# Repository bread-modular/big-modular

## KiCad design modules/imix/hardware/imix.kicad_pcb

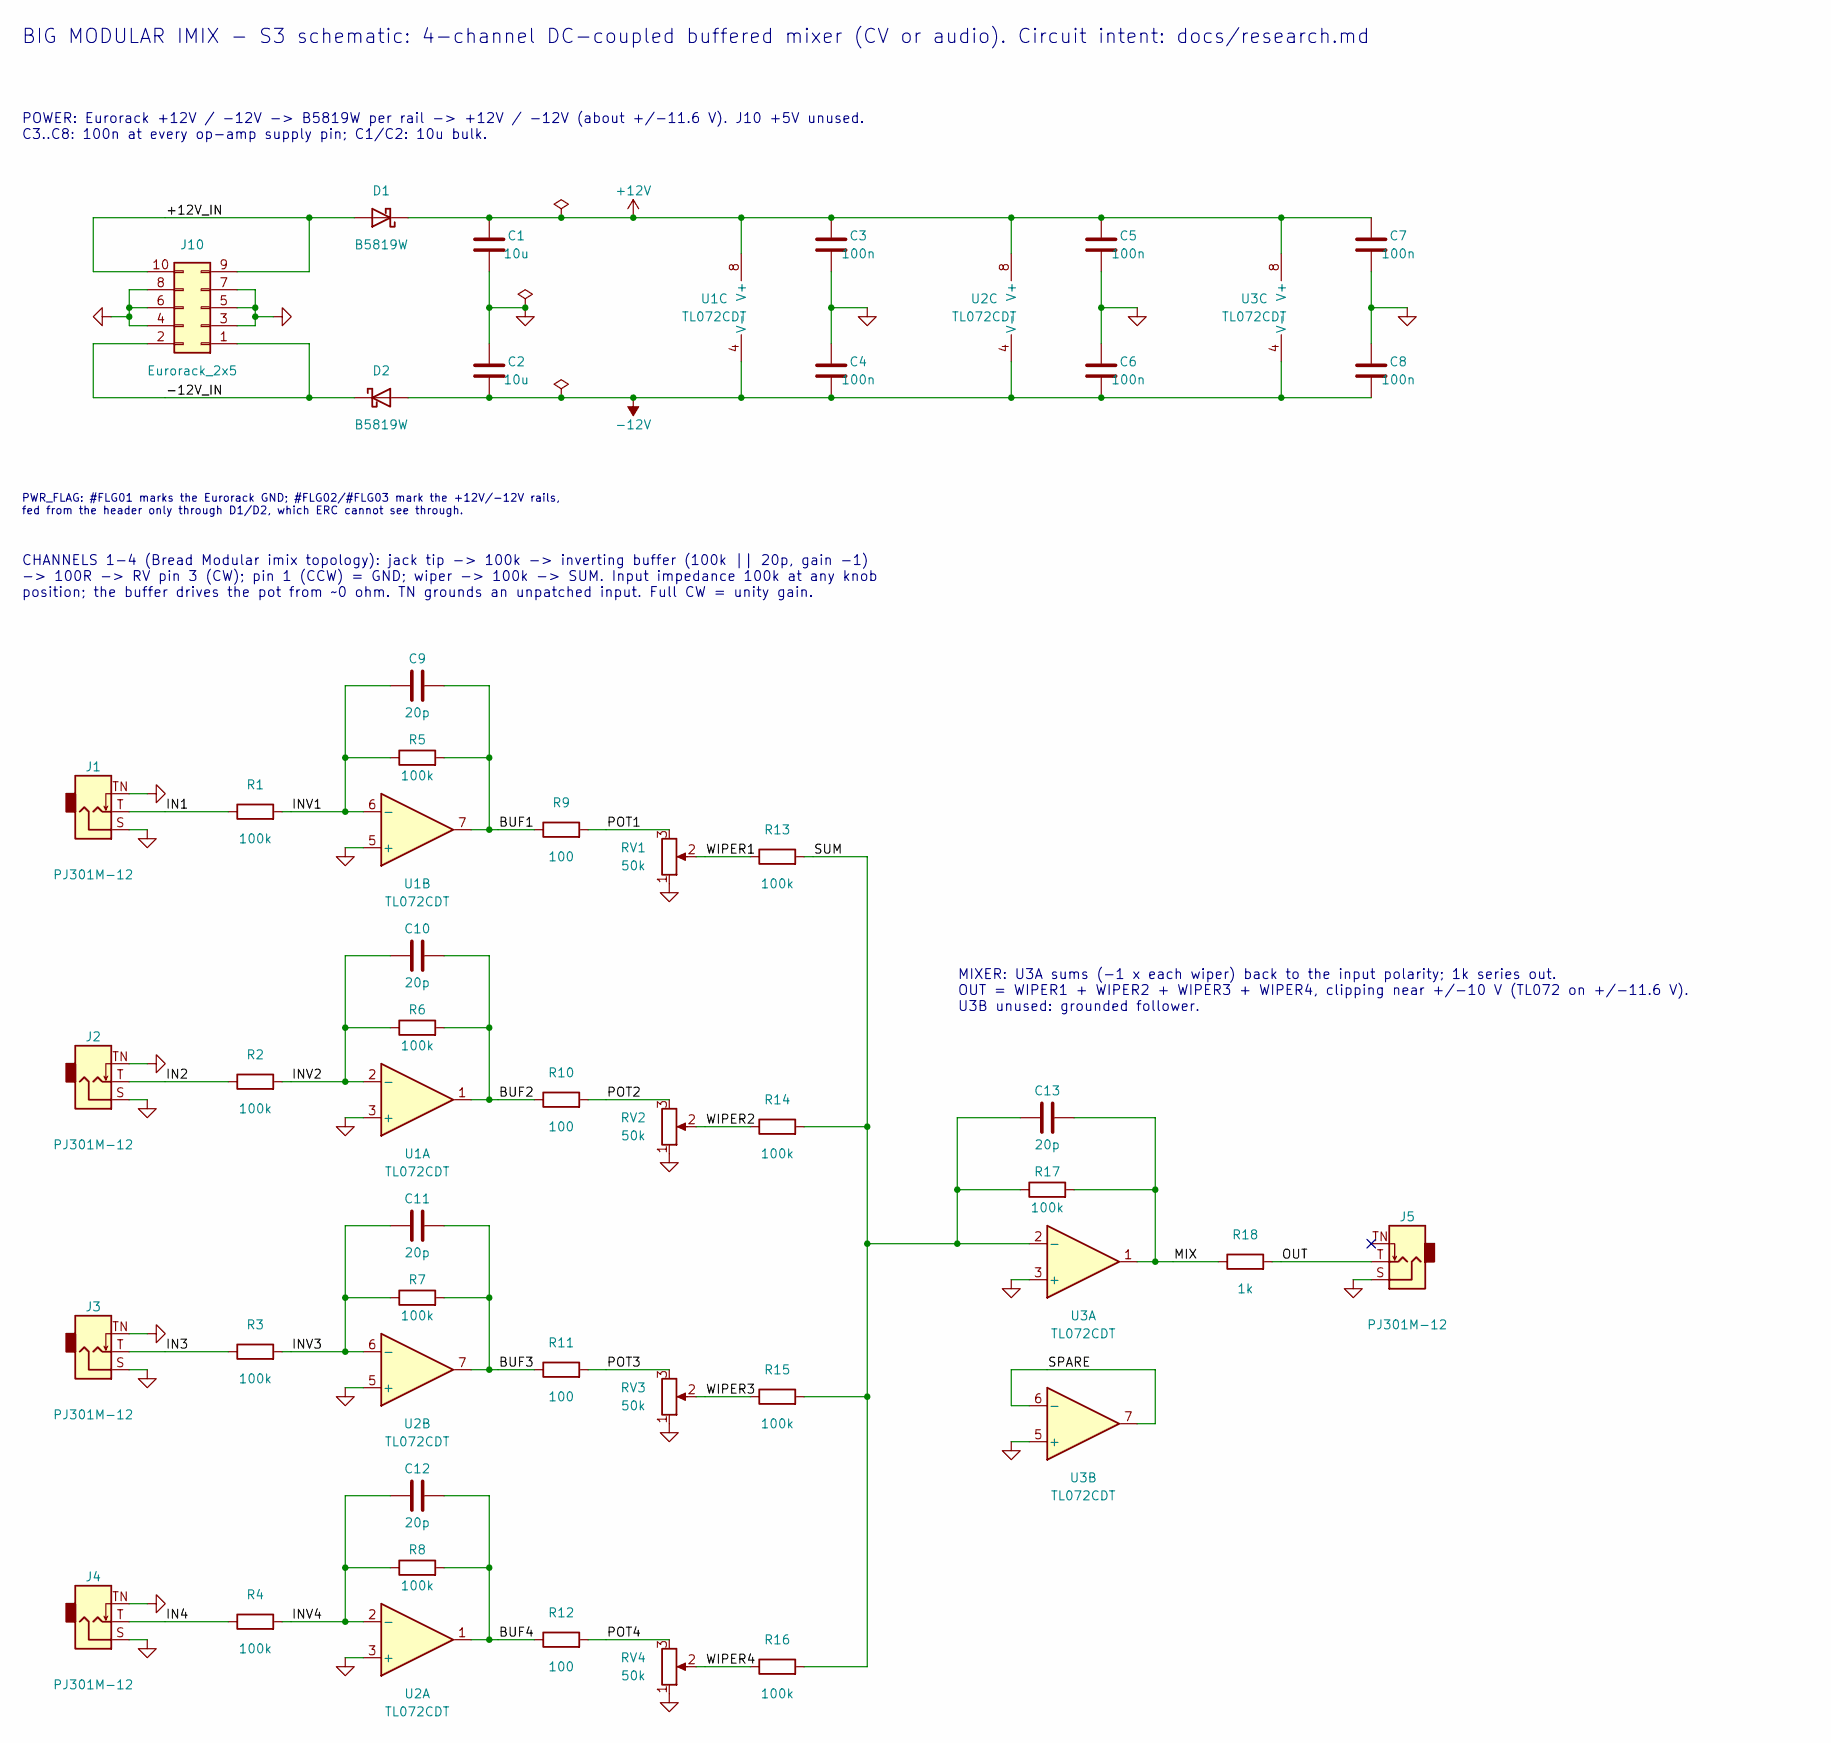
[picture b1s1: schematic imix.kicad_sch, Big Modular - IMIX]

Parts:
C1, C2: 10u; C_0805_2012Metric; Voltage 25V; MPN CL21A106KAYNNNE; LCSC C15850
C3, C4, C5, C6, C7, C8: 100n; C_0603_1608Metric; Voltage 50V; MPN CC0603KRX7R9BB104; LCSC C14663
C9, C10, C11, C12, C13: 20p; C_0603_1608Metric; Voltage 50V; MPN CL10C200JB8NNNC; LCSC C1648
D1, D2: B5819W; D_SOD-123; MPN B5819W SL; LCSC C8598
J1, J2, J3, J4, J5: PJ301M-12; Jack_3.5mm_QingPu_WQP-PJ301M-12_Vertical
J10: Eurorack_2x5; PinHeader_2x05_P2.54mm_Vertical
R1, R2, R3, R4, R5, R6, R7, R8, R13, R14, R15, R16, R17: 100k; R_0603_1608Metric; MPN 0603WAF1003T5E; LCSC C25803
R9, R10, R11, R12: 100; R_0603_1608Metric; MPN 0603WAF1000T5E; LCSC C22775
R18: 1k; R_2512_6332Metric; MPN 25121WF1001T4E; LCSC C54315
RV1, RV2, RV3, RV4: 50k; Potentiometer_RV09
U1, U2, U3: TL072CDT; SOIC-8_3.9x4.9mm_P1.27mm; MPN TL072CDT; LCSC C6961

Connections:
+12V: C1.1, C3.1, C5.1, C7.1, D1.1 (K), U1.8 (V+), U2.8 (V+), U3.8 (V+)
-12V: C2.2, C4.2, C6.2, C8.2, D2.2 (A), U1.4 (V-), U2.4 (V-), U3.4 (V-)
/+12V_IN: D1.2 (A), J10.9, J10.10
/-12V_IN: D2.1 (K), J10.1, J10.2
/BUF1: C9.2, R5.2, R9.1, U1.7
/BUF2: C10.2, R6.2, R10.1, U1.1
/BUF3: C11.2, R7.2, R11.1, U2.7
/BUF4: C12.2, R8.2, R12.1, U2.1
/IN1: J1.T, R1.1
/IN2: J2.T, R2.1
/IN3: J3.T, R3.1
/IN4: J4.T, R4.1
/INV1: C9.1, R1.2, R5.1, U1.6 (-)
/INV2: C10.1, R2.2, R6.1, U1.2 (-)
/INV3: C11.1, R3.2, R7.1, U2.6 (-)
/INV4: C12.1, R4.2, R8.1, U2.2 (-)
/MIX: C13.2, R17.2, R18.1, U3.1
/OUT: J5.T, R18.2
/POT1: R9.2, RV1.3
/POT2: R10.2, RV2.3
/POT3: R11.2, RV3.3
/POT4: R12.2, RV4.3
/SPARE: U3.6 (-), U3.7
/SUM: C13.1, R13.2, R14.2, R15.2, R16.2, R17.1, U3.2 (-)
/WIPER1: R13.1, RV1.2
/WIPER2: R14.1, RV2.2
/WIPER3: R15.1, RV3.2
/WIPER4: R16.1, RV4.2
GND: C1.2, C2.1, C3.2, C4.1, C5.2, C6.1, C7.2, C8.1, J1.S, J1.TN, J2.S, J2.TN, J3.S, J3.TN, J4.S, J4.TN, J5.S, J10.3, J10.4, J10.5, J10.6, J10.7, J10.8, RV1.1, RV2.1, RV3.1, RV4.1, U1.3 (+), U1.5 (+), U2.3 (+), U2.5 (+), U3.3 (+), U3.5 (+)

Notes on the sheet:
MIXER: U3A sums (-1 x each wiper) back to the input polarity; 1k series out. OUT = WIPER1 + WIPER2 + WIPER3 + WIPER4, clipping near +/-10 V (TL072 on +/-11.6 V). U3B unused: grounded follower.
BIG MODULAR IMIX - S3 schematic: 4-channel DC-coupled buffered mixer (CV or audio). Circuit intent: docs/research.md
CHANNELS 1-4 (Bread Modular imix topology): jack tip -> 100k -> inverting buffer (100k || 20p, gain -1) -> 100R -> RV pin 3 (CW); pin 1 (CCW) = GND; wiper -> 100k -> SUM. Input impedance 100k at any knob position; the buffer drives the pot from ~0 ohm. TN grounds an unpatched input. Full CW = unity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
PWR_FLAG: #FLG01 marks the Eurorack GND; #FLG02/#FLG03 mark the +12V/-12V rails, fed from the header only through D1/D2, which ERC cannot see through.
POWER: Eurorack +12V / -12V -> B5819W per rail -> +12V / -12V (about +/-11.6 V). J10 +5V unused. C3..C8: 100n at every op-amp supply pin; C1/C2: 10u bulk.

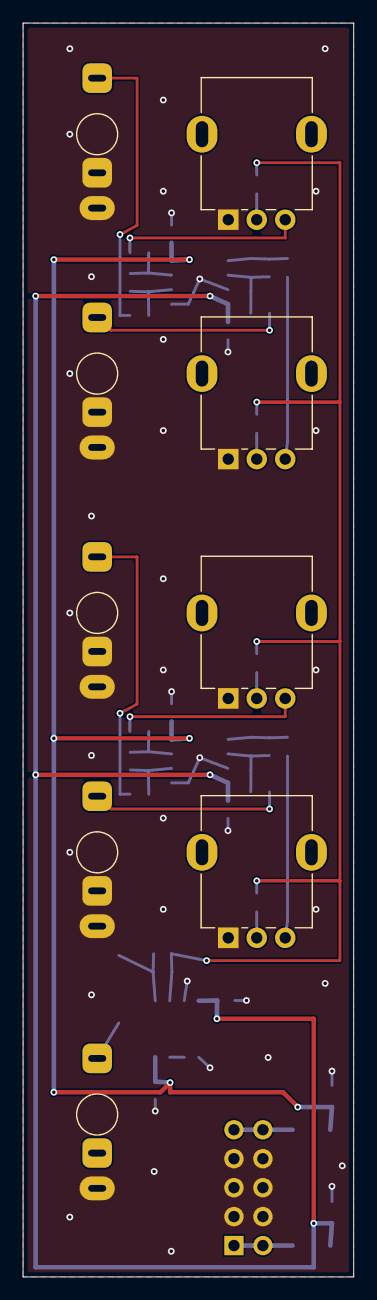
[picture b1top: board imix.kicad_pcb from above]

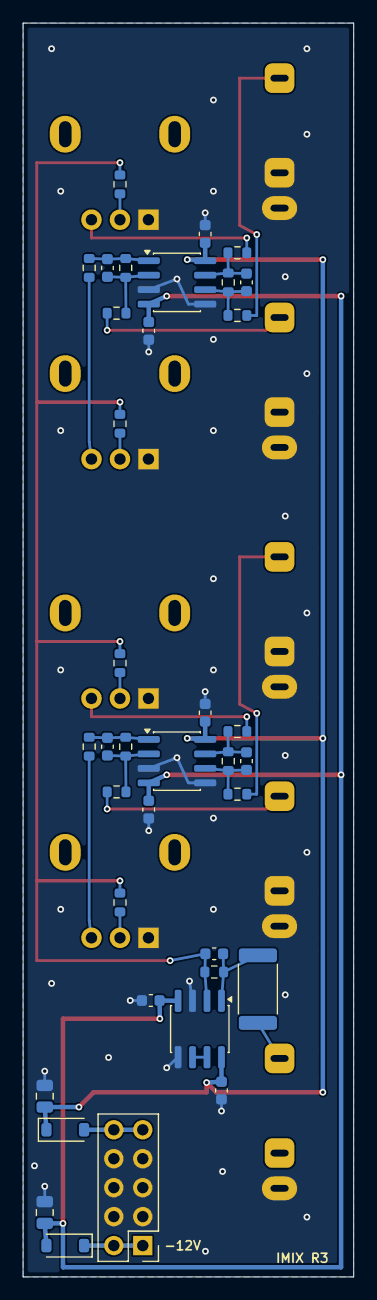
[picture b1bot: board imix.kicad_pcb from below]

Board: 2 copper layers, 29.0 x 110.0 mm, 46 parts (37 on the bottom side), 29 nets.

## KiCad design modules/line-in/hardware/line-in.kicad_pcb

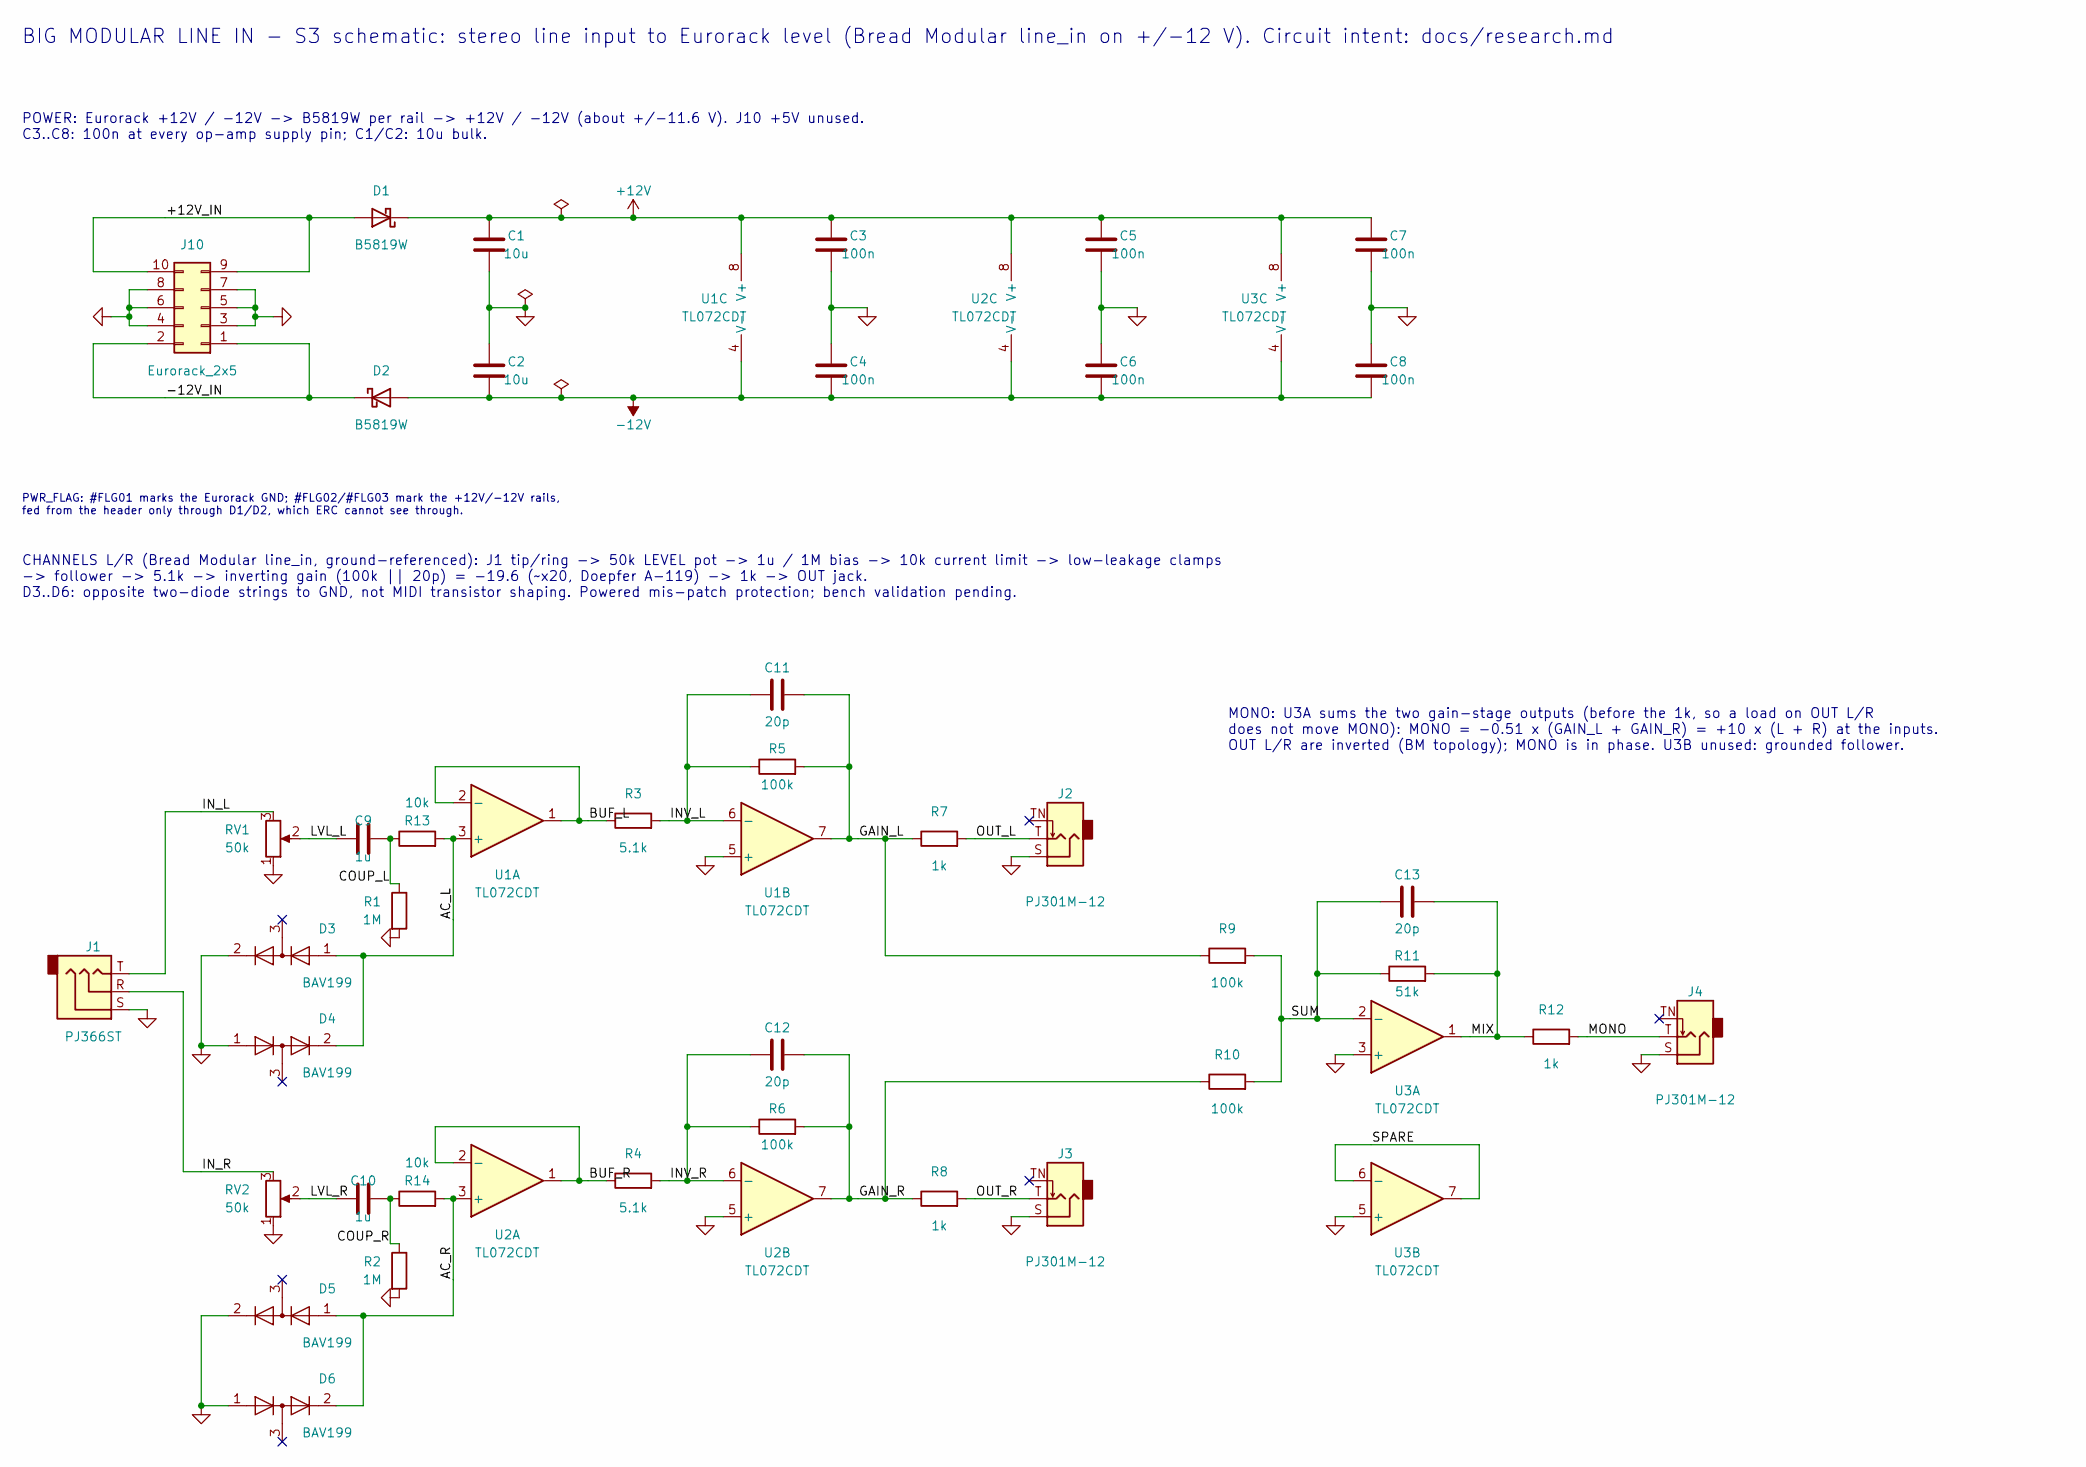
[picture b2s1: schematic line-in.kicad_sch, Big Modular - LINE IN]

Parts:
C1, C2: 10u; C_0805_2012Metric; Voltage 25V; MPN CL21A106KAYNNNE; LCSC C15850
C3, C4, C5, C6, C7, C8: 100n; C_0603_1608Metric; Voltage 50V; MPN CC0603KRX7R9BB104; LCSC C14663
C9, C10: 1u; C_0805_2012Metric; Voltage 50V; MPN CL21B105KBFNNNE; LCSC C28323
C11, C12, C13: 20p; C_0603_1608Metric; Voltage 50V; MPN CL10C200JB8NNNC; LCSC C1648
D1, D2: B5819W; D_SOD-123; MPN B5819W SL; LCSC C8598
D3, D4, D5, D6: BAV199; SOT-23; MPN BAV199,215; LCSC C40919
J1: PJ366ST; Jack_3.5mm_QingPu_WQP-PJ366ST_Vertical
J2, J3, J4: PJ301M-12; Jack_3.5mm_QingPu_WQP-PJ301M-12_Vertical
J10: Eurorack_2x5; PinHeader_2x05_P2.54mm_Vertical
R1, R2: 1M; R_0603_1608Metric; MPN 0603WAF1004T5E; LCSC C22935
R3, R4: 5.1k; R_0603_1608Metric; MPN 0603WAF5101T5E; LCSC C23186
R5, R6, R9, R10: 100k; R_0603_1608Metric; MPN 0603WAF1003T5E; LCSC C25803
R7, R8, R12: 1k; R_1206_3216Metric; MPN ESR18EZPF1001; LCSC C2074262
R11: 51k; R_0603_1608Metric; MPN 0603WAF5102T5E; LCSC C23196
R13, R14: 10k; R_0603_1608Metric; MPN 0603WAF1002T5E; LCSC C25804
RV1, RV2: 50k; Potentiometer_RV09
U1, U2, U3: TL072CDT; SOIC-8_3.9x4.9mm_P1.27mm; MPN TL072CDT; LCSC C6961

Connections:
+12V: C1.1, C3.1, C5.1, C7.1, D1.1 (K), U1.8 (V+), U2.8 (V+), U3.8 (V+)
-12V: C2.2, C4.2, C6.2, C8.2, D2.2 (A), U1.4 (V-), U2.4 (V-), U3.4 (V-)
/+12V_IN: D1.2 (A), J10.9, J10.10
/-12V_IN: D2.1 (K), J10.1, J10.2
/AC_L: D3.1 (K), D4.2 (A), R13.2, U1.3 (+)
/AC_R: D5.1 (K), D6.2 (A), R14.2, U2.3 (+)
/BUF_L: R3.1, U1.1, U1.2 (-)
/BUF_R: R4.1, U2.1, U2.2 (-)
/COUP_L: C9.2, R1.1, R13.1
/COUP_R: C10.2, R2.1, R14.1
/GAIN_L: C11.2, R5.2, R7.1, R9.1, U1.7
/GAIN_R: C12.2, R6.2, R8.1, R10.1, U2.7
/INV_L: C11.1, R3.2, R5.1, U1.6 (-)
/INV_R: C12.1, R4.2, R6.1, U2.6 (-)
/IN_L: J1.T, RV1.3
/IN_R: J1.R, RV2.3
/LVL_L: C9.1, RV1.2
/LVL_R: C10.1, RV2.2
/MIX: C13.2, R11.2, R12.1, U3.1
/MONO: J4.T, R12.2
/OUT_L: J2.T, R7.2
/OUT_R: J3.T, R8.2
/SPARE: U3.6 (-), U3.7
/SUM: C13.1, R9.2, R10.2, R11.1, U3.2 (-)
GND: C1.2, C2.1, C3.2, C4.1, C5.2, C6.1, C7.2, C8.1, D3.2 (A), D4.1 (K), D5.2 (A), D6.1 (K), J1.S, J2.S, J3.S, J4.S, J10.3, J10.4, J10.5, J10.6, J10.7, J10.8, R1.2, R2.2, RV1.1, RV2.1, U1.5 (+), U2.5 (+), U3.3 (+), U3.5 (+)

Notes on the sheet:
MONO: U3A sums the two gain-stage outputs (before the 1k, so a load on OUT L/R does not move MONO): MONO = -0.51 x (GAIN_L + GAIN_R) = +10 x (L + R) at the inputs. OUT L/R are inverted (BM topology); MONO is in phase. U3B unused: grounded follower.
POWER: Eurorack +12V / -12V -> B5819W per rail -> +12V / -12V (about +/-11.6 V). J10 +5V unused. C3..C8: 100n at every op-amp supply pin; C1/C2: 10u bulk.
BIG MODULAR LINE IN - S3 schematic: stereo line input to Eurorack level (Bread Modular line_in on +/-12 V). Circuit intent: docs/research.md
PWR_FLAG: #FLG01 marks the Eurorack GND; #FLG02/#FLG03 mark the +12V/-12V rails, fed from the header only through D1/D2, which ERC cannot see through.
CHANNELS L/R (Bread Modular line_in, ground-referenced): J1 tip/ring -> 50k LEVEL pot -> 1u / 1M bias -> 10k current limit -> low-leakage clamps -> follower -> 5.1k -> inverting gain (100k || 20p) = -19.6 (~x20, Doepfer A-119) -> 1k -> OUT jack. D3..D6: opposite two-diode strings to GND, not MIDI t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

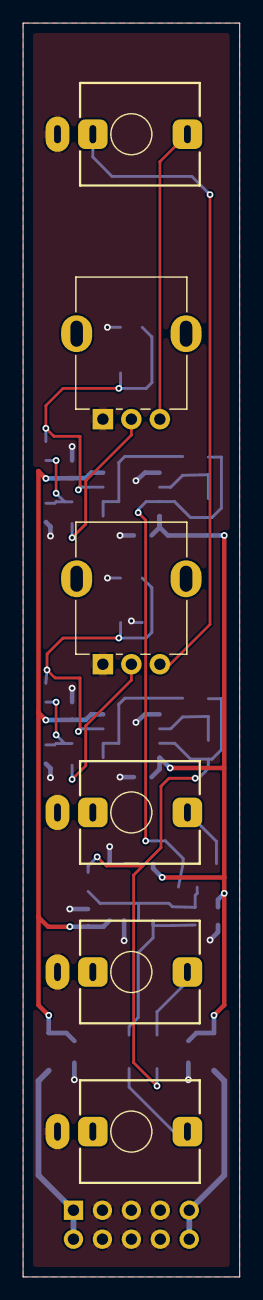
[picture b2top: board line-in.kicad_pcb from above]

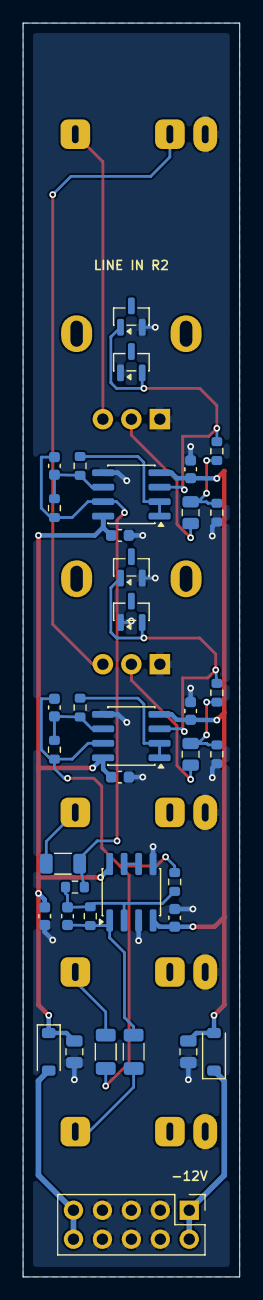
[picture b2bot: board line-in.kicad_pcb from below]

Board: 2 copper layers, 19.0 x 110.0 mm, 43 parts (37 on the bottom side), 25 nets.

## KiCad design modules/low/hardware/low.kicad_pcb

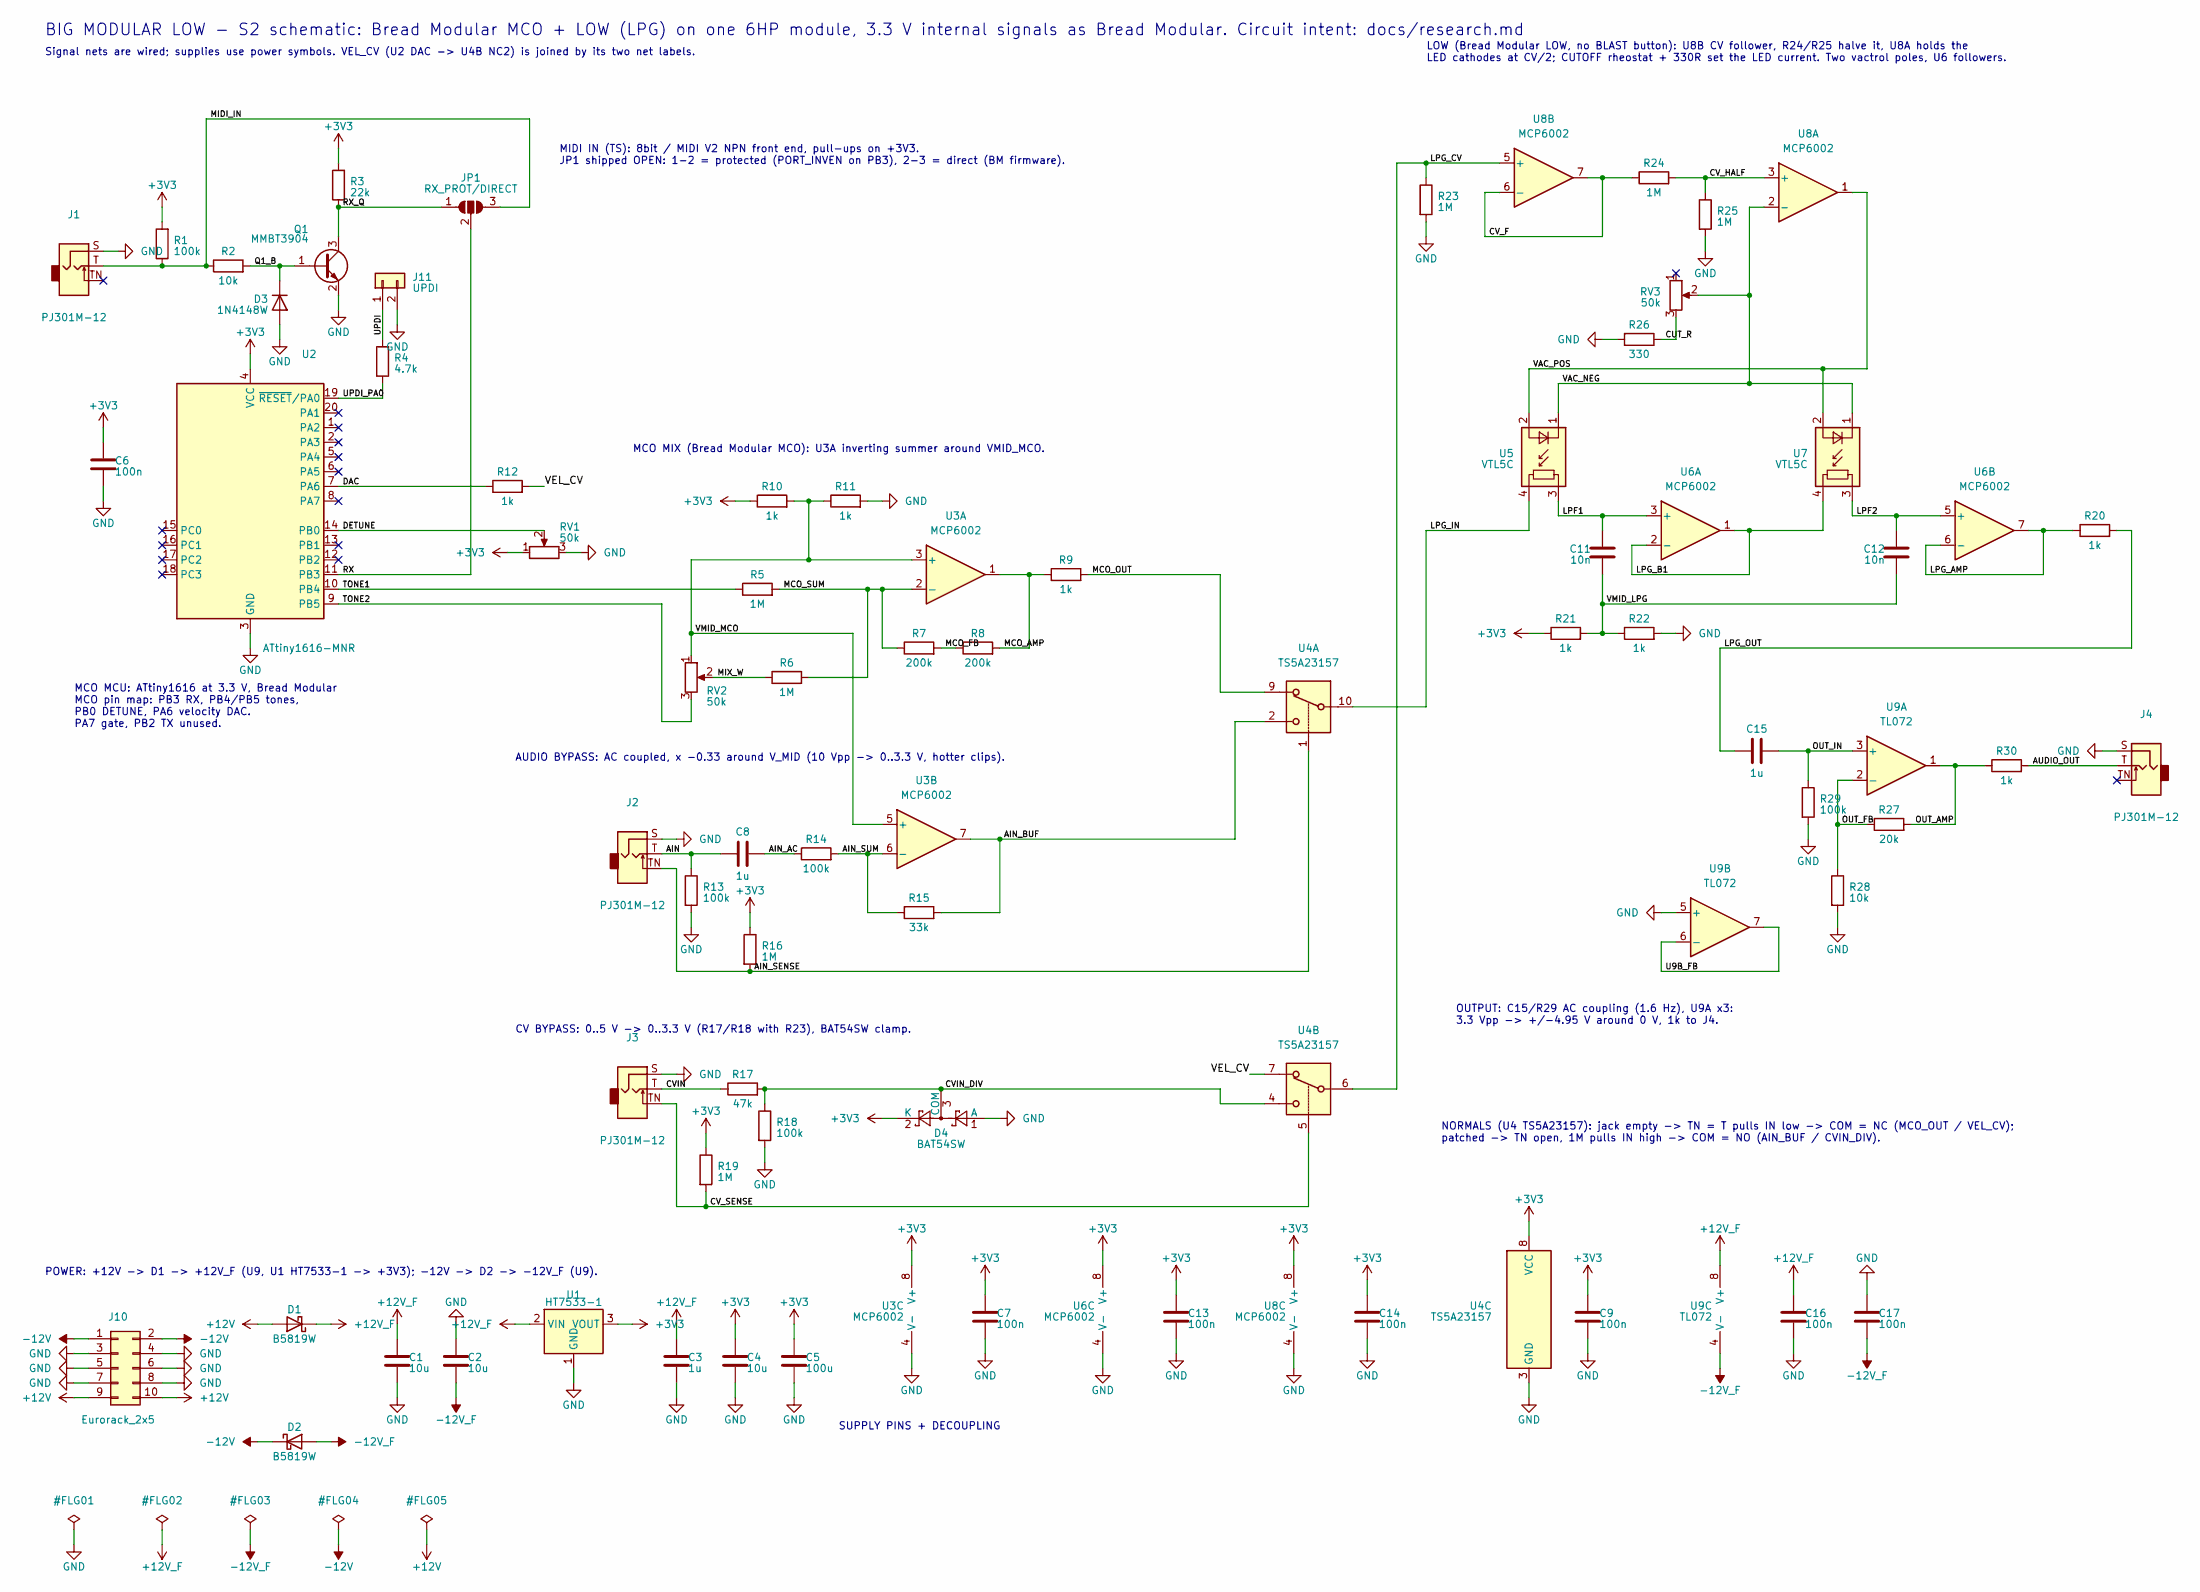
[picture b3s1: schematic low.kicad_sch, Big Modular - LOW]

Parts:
C1, C2, C4: 10u; C_0805_2012Metric; Voltage 25V; MPN CL21A106KAYNNNE; LCSC C15850
C3, C8: 1u; C_0805_2012Metric; Voltage 50V; MPN CL21B105KBFNNNE; LCSC C28323
C5: 100u; C_1206_3216Metric; Voltage 6.3V; MPN CL31A107MQHNNNE; LCSC C15008
C6, C7, C9, C13, C14, C16, C17: 100n; C_0603_1608Metric; Voltage 50V; MPN CC0603KRX7R9BB104; LCSC C14663
C11, C12: 10n; C_0603_1608Metric; Voltage 50V; MPN 0603B103K500NT; LCSC C57112
C15: 1u; C_0805_2012Metric; Voltage 25V; MPN CL21B105KBFNNNE; LCSC C28323
D1, D2: B5819W; D_SOD-123; MPN B5819W SL; LCSC C8598
D3: 1N4148W; D_SOD-123; MPN 1N4148W; LCSC C81598
D4: BAT54SW; SOT-323_SC-70; MPN BAT54SWT1G; LCSC C78260
J1, J2, J3, J4: PJ301M-12; Jack_3.5mm_QingPu_WQP-PJ301M-12_Vertical
J10: Eurorack_2x5; PinHeader_2x05_P2.54mm_Vertical
J11: UPDI; PinHeader_1x02_P2.54mm_Vertical
JP1: RX_PROT/DIRECT; SolderJumper-3_P1.3mm_Open_RoundedPad1.0x1.5mm
Q1: MMBT3904; SOT-23; MPN MMBT3904(RANGE:100-300); LCSC C20526
R1, R13, R14, R18, R29: 100k; R_0603_1608Metric; MPN 0603WAF1003T5E; LCSC C25803
R2, R28: 10k; R_0603_1608Metric; MPN 0603WAF1002T5E; LCSC C25804
R3: 22k; R_0603_1608Metric; MPN 0603WAF2202T5E; LCSC C31850
R4: 4.7k; R_0603_1608Metric; MPN 0603WAF4701T5E; LCSC C23162
R5, R6, R16, R19, R23, R24, R25: 1M; R_0603_1608Metric; MPN 0603WAF1004T5E; LCSC C22935
R7, R8: 200k; R_0603_1608Metric; MPN 0603WAF2003T5E; LCSC C25811
R9, R10, R11, R12, R20, R21, R22: 1k; R_0603_1608Metric; MPN 0603WAF1001T5E; LCSC C21190
R15: 33k; R_0603_1608Metric; MPN 0603WAF3302T5E; LCSC C4216
R17: 47k; R_0603_1608Metric; MPN 0603WAF4702T5E; LCSC C25819
R26: 330; R_0603_1608Metric; MPN 0603WAF3300T5E; LCSC C23138
R27: 20k; R_0603_1608Metric; MPN 0603WAF2002T5E; LCSC C4184
R30: 1k; R_1206_3216Metric; MPN 1206W4F1001T5E; LCSC C4410
RV1, RV2, RV3: 50k; Potentiometer_RV09
U1: HT7533-1; SOT-89-3; MPN HT7533-1; LCSC C14289
U2: ATtiny1616-MNR; VQFN-20-1EP_3x3mm_P0.4mm_EP1.7x1.7mm; MPN ATTINY1616-MNR; LCSC C507118
U3, U6, U8: MCP6002; SOIC-8_3.9x4.9mm_P1.27mm; MPN MCP6002T-I/SN; LCSC C7377
U4: TS5A23157; TSSOP-10_3x3mm_P0.5mm; MPN TS5A23157DGSR; LCSC C11133
U5, U7: VTL5C
U9: TL072; SOIC-8_3.9x4.9mm_P1.27mm; MPN TL072CDT; LCSC C6961

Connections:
+3V3: C4.1, C5.1, C6.1, C7.1, C9.1, C13.1, C14.1, D4.2 (K), R1.2, R3.2, R10.1, R16.1, R19.1, R21.1, RV1.1, U1.3 (VOUT), U2.4 (VCC), U3.8 (V+), U4.8 (VCC), U6.8 (V+), U8.8 (V+)
+12V: D1.2 (A), J10.9, J10.10
+12V_F: C1.1, C3.1, C16.1, D1.1 (K), U1.2 (VIN), U9.8 (V+)
-12V: D2.1 (K), J10.1, J10.2
-12V_F: C2.2, C17.2, D2.2 (A), U9.4 (V-)
/AIN: C8.1, J2.T, R13.1
/AIN_AC: C8.2, R14.1
/AIN_BUF: R15.2, U3.7, U4.2
/AIN_SENSE: J2.TN, R16.2, U4.1
/AIN_SUM: R14.2, R15.1, U3.6 (-)
/AUDIO_OUT: J4.T, R30.2
/CUT_R: R26.1, RV3.3
/CVIN: J3.T, R17.1
/CVIN_DIV: D4.3 (COM), R17.2, R18.1, U4.4
/CV_F: R24.1, U8.6 (-), U8.7
/CV_HALF: R24.2, R25.1, U8.3 (+)
/CV_SENSE: J3.TN, R19.2, U4.5
/DAC: R12.1, U2.7 (PA6)
/DETUNE: RV1.2, U2.14 (PB0)
/LPF1: C11.1, U5.3, U6.3 (+)
/LPF2: C12.1, U6.5 (+), U7.3
/LPG_AMP: R20.1, U6.6 (-), U6.7
/LPG_B1: U6.1, U6.2 (-), U7.4
/LPG_CV: R23.1, U4.6, U8.5 (+)
/LPG_IN: U4.10, U5.4
/LPG_OUT: C15.1, R20.2
/MCO_AMP: R8.2, R9.1, U3.1
/MCO_FB: R7.2, R8.1
/MCO_OUT: R9.2, U4.9
/MCO_SUM: R5.2, R6.2, R7.1, U3.2 (-)
/MIDI_IN: J1.T, JP1.3 (B), R1.1, R2.1
/MIX_W: R6.1, RV2.2
/OUT_AMP: R27.2, R30.1, U9.1
/OUT_FB: R27.1, R28.1, U9.2 (-)
/OUT_IN: C15.2, R29.1, U9.3 (+)
/Q1_B: D3.1 (K), Q1.1 (B), R2.2
/RX: JP1.2 (C), U2.11 (PB3)
/RX_Q: JP1.1 (A), Q1.3 (C), R3.1
/TONE1: R5.1, U2.10 (PB4)
/TONE2: RV2.3, U2.9 (PB5)
/U9B_FB: U9.6 (-), U9.7
/UPDI: J11.1, R4.2
/UPDI_PA0: R4.1, U2.19 (~RESET/PA0)
/VAC_NEG: RV3.2, U5.1 (-), U7.1 (-), U8.2 (-)
/VAC_POS: U5.2 (+), U7.2 (+), U8.1
/VEL_CV: R12.2, U4.7
/VMID_LPG: C11.2, C12.2, R21.2, R22.1
/VMID_MCO: R10.2, R11.1, RV2.1, U3.3 (+), U3.5 (+)
GND: C1.2, C2.1, C3.2, C4.2, C5.2, C6.2, C7.2, C9.2, C13.2, C14.2, C16.2, C17.1, D3.2 (A), D4.1 (A), J1.S, J2.S, J3.S, J4.S, J10.3, J10.4, J10.5, J10.6, J10.7, J10.8, J11.2, Q1.2 (E), R11.2, R13.2, R18.2, R22.2, R23.2, R25.2, R26.2, R28.2, R29.2, RV1.3, U1.1 (GND), U2.3 (GND), U2.21 (GND), U3.4 (V-), U4.3 (GND), U6.4 (V-), U8.4 (V-), U9.5 (+)

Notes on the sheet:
NORMALS (U4 TS5A23157): jack empty -> TN = T pulls IN low -> COM = NC (MCO_OUT / VEL_CV); patched -> TN open, 1M pulls IN high -> COM = NO (AIN_BUF / CVIN_DIV).
SUPPLY PINS + DECOUPLING
LOW (Bread Modular LOW, no BLAST button): U8B CV follower, R24/R25 halve it, U8A holds the LED cathodes at CV/2; CUTOFF rheostat + 330R set the LED current. Two vactrol poles, U6 followers.
Signal nets are wired; supplies use power symbols. VEL_CV (U2 DAC -> U4B NC2) is joined by its two net labels.
MIDI IN (TS): 8bit / MIDI V2 NPN front end, pull-ups on +3V3. JP1 shipped OPEN: 1-2 = protected (PORT_INVEN on PB3), 2-3 = direct (BM firmware).
MCO MCU: ATtiny1616 at 3.3 V, Bread Modular MCO pin map: PB3 RX, PB4/PB5 tones, PB0 DETUNE, PA6 velocity DAC. PA7 gate, PB2 TX unused.
OUTPUT: C15/R29 AC coupling (1.6 Hz), U9A x3: 3.3 Vpp -> +/-4.95 V around 0 V, 1k to J4.
BIG MODULAR LOW - S2 schematic: Bread Modular MCO + LOW (LPG) on one 6HP module, 3.3 V internal signals as Bread Modular. Circuit intent: docs/research.md
AUDIO BYPASS: AC coupled, x -0.33 around V_MID (10 Vpp -> 0..3.3 V, hotter clips).
POWER: +12V -> D1 -> +12V_F (U9, U1 HT7533-1 -> +3V3); -12V -> D2 -> -12V_F (U9).
MCO MIX (Bread Modular MCO): U3A inverting summer around VMID_MCO.
CV BYPASS: 0..5 V -> 0..3.3 V (R17/R18 with R23), BAT54SW clamp.

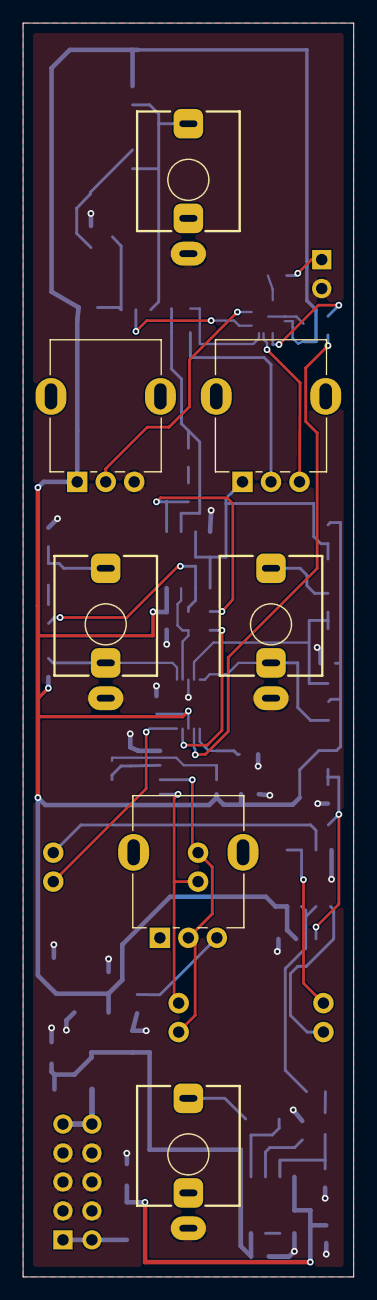
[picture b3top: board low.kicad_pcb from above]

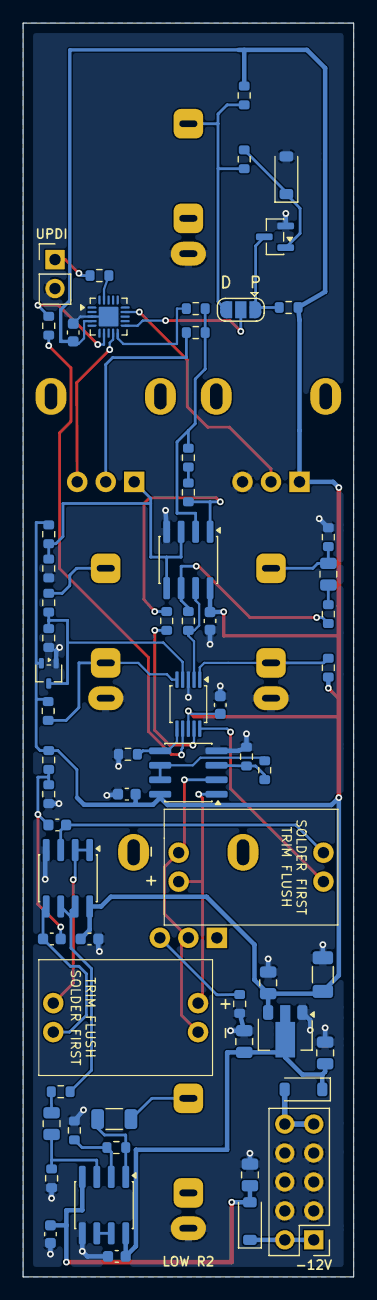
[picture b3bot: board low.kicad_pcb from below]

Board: 2 copper layers, 29.0 x 110.0 mm, 70 parts (63 on the bottom side), 49 nets.
